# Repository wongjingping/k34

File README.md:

# k34

This project contains the pcb designs for the k34 keyboard. The k34 is a unibody, column-staggered, high-profile, 3d-printed, tray-mount keyboard with 34 keys.

`orient.py` contains a python script I used to programmatically arrange the switch and diode footprints. Traces were hand-connected.

`k34/plate and case reference` contains the exported svg's that I imported into fusion360 for modeling the case and plate files. 

`case` contains the stl files I used for the plate and case. The case supports the sides/outline of the pcb and fits well but isn't secured (ie would be fine if you're not planning to transport/move it around a lot). Note that the plate is non-symmetric and is adapted directly from the pcb's edge cut layer. 

## Firmware

- [zmk](https://github.com/wongjingping/zmk-config)

- [qmk](https://github.com/qmk/qmk_firmware/tree/master/keyboards/k34)

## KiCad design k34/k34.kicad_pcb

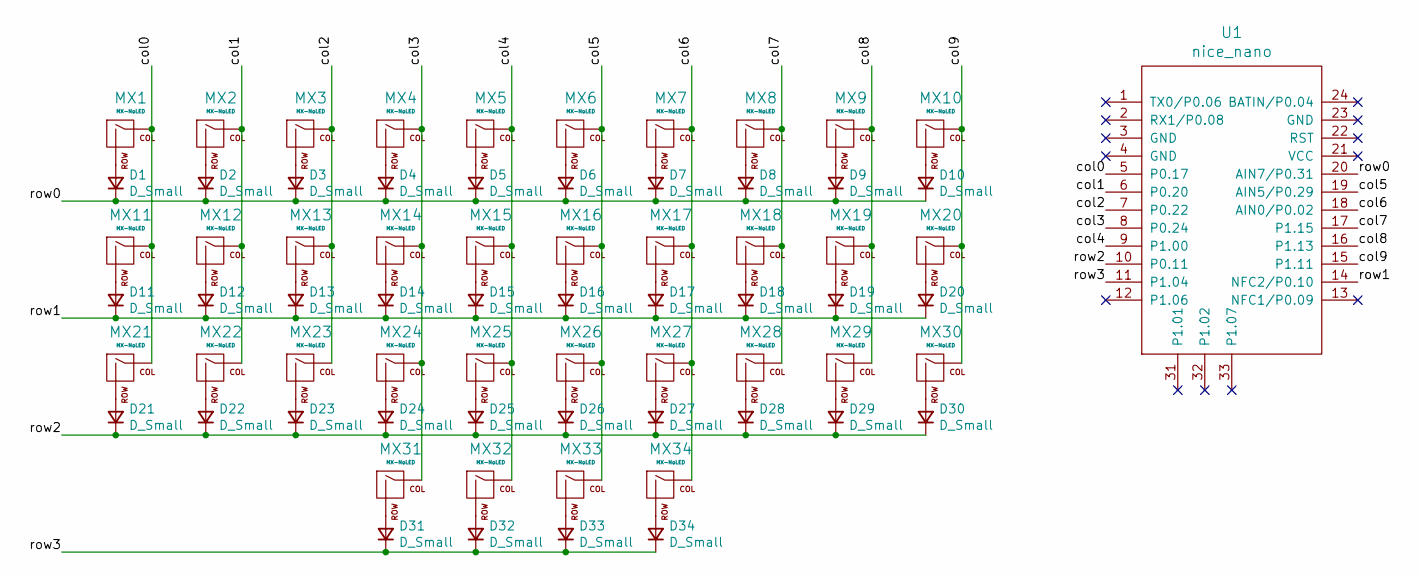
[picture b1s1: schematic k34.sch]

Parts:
D1, D2, D3, D4, D5, D6, D7, D8, D9, D10, D11, D12, D13, D14, D15, D16, D17, D18, D19, D20, D21, D22, D23, D24, D25, D26, D27, D28, D29, D30, D31, D32, D33, D34: D_Small; D_SOD-128
MX1, MX2, MX3, MX4, MX5, MX6, MX7, MX8, MX9, MX10, MX11, MX12, MX13, MX14, MX15, MX16, MX17, MX18, MX19, MX20, MX21, MX22, MX23, MX24, MX25, MX26, MX27, MX28, MX29, MX30, MX31, MX32, MX33, MX34: MX-NoLED; MXOnly-1U-Hotswap
U1: nice_nano

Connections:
/col0: MX1.1 (COL), MX11.1 (COL), MX21.1 (COL), U1.5 (P0.17)
/col1: MX2.1 (COL), MX12.1 (COL), MX22.1 (COL), U1.6 (P0.20)
/col2: MX3.1 (COL), MX13.1 (COL), MX23.1 (COL), U1.7 (P0.22)
/col3: MX4.1 (COL), MX14.1 (COL), MX24.1 (COL), MX31.1 (COL), U1.8 (P0.24)
/col4: MX5.1 (COL), MX15.1 (COL), MX25.1 (COL), MX32.1 (COL), U1.9 (P1.00)
/col5: MX6.1 (COL), MX16.1 (COL), MX26.1 (COL), MX33.1 (COL), U1.19 (AIN5/P0.29)
/col6: MX7.1 (COL), MX17.1 (COL), MX27.1 (COL), MX34.1 (COL), U1.18 (AIN0/P0.02)
/col7: MX8.1 (COL), MX18.1 (COL), MX28.1 (COL), U1.17 (P1.15)
/col8: MX9.1 (COL), MX19.1 (COL), MX29.1 (COL), U1.16 (P1.13)
/col9: MX10.1 (COL), MX20.1 (COL), MX30.1 (COL), U1.15 (P1.11)
/row0: D1.1 (K), D2.1 (K), D3.1 (K), D4.1 (K), D5.1 (K), D6.1 (K), D7.1 (K), D8.1 (K), D9.1 (K), D10.1 (K), U1.20 (AIN7/P0.31)
/row1: D11.1 (K), D12.1 (K), D13.1 (K), D14.1 (K), D15.1 (K), D16.1 (K), D17.1 (K), D18.1 (K), D19.1 (K), D20.1 (K), U1.14 (NFC2/P0.10)
/row2: D21.1 (K), D22.1 (K), D23.1 (K), D24.1 (K), D25.1 (K), D26.1 (K), D27.1 (K), D28.1 (K), D29.1 (K), D30.1 (K), U1.10 (P0.11)
/row3: D31.1 (K), D32.1 (K), D33.1 (K), D34.1 (K), U1.11 (P1.04)
unnamed: D1.2 (A), MX1.2 (ROW)
unnamed: D2.2 (A), MX2.2 (ROW)
unnamed: D3.2 (A), MX3.2 (ROW)
unnamed: D4.2 (A), MX4.2 (ROW)
unnamed: D5.2 (A), MX5.2 (ROW)
unnamed: D6.2 (A), MX6.2 (ROW)
unnamed: D7.2 (A), MX7.2 (ROW)
unnamed: D8.2 (A), MX8.2 (ROW)
unnamed: D9.2 (A), MX9.2 (ROW)
unnamed: D10.2 (A), MX10.2 (ROW)
unnamed: D11.2 (A), MX11.2 (ROW)
unnamed: D12.2 (A), MX12.2 (ROW)
unnamed: D13.2 (A), MX13.2 (ROW)
unnamed: D14.2 (A), MX14.2 (ROW)
unnamed: D15.2 (A), MX15.2 (ROW)
unnamed: D16.2 (A), MX16.2 (ROW)
unnamed: D17.2 (A), MX17.2 (ROW)
unnamed: D18.2 (A), MX18.2 (ROW)
unnamed: D19.2 (A), MX19.2 (ROW)
unnamed: D20.2 (A), MX20.2 (ROW)
unnamed: D21.2 (A), MX21.2 (ROW)
unnamed: D22.2 (A), MX22.2 (ROW)
unnamed: D23.2 (A), MX23.2 (ROW)
unnamed: D24.2 (A), MX24.2 (ROW)
unnamed: D25.2 (A), MX25.2 (ROW)
unnamed: D26.2 (A), MX26.2 (ROW)
unnamed: D27.2 (A), MX27.2 (ROW)
unnamed: D28.2 (A), MX28.2 (ROW)
unnamed: D29.2 (A), MX29.2 (ROW)
unnamed: D30.2 (A), MX30.2 (ROW)
unnamed: D31.2 (A), MX31.2 (ROW)
unnamed: D32.2 (A), MX32.2 (ROW)
unnamed: D33.2 (A), MX33.2 (ROW)
unnamed: D34.2 (A), MX34.2 (ROW)

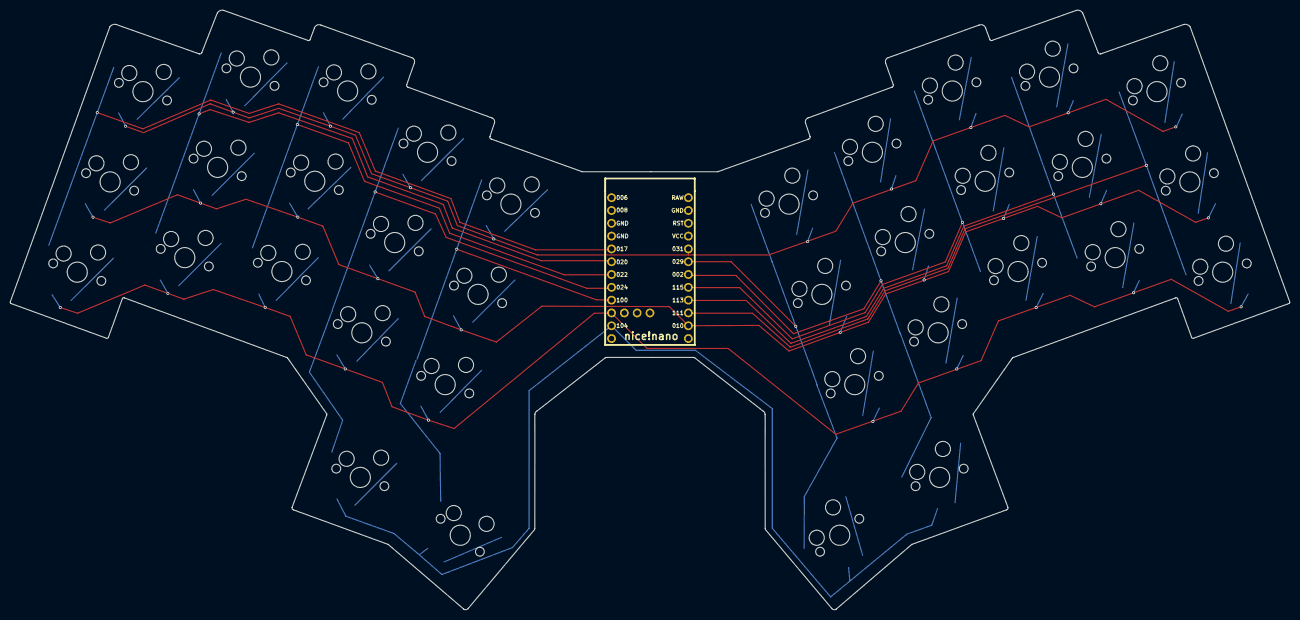
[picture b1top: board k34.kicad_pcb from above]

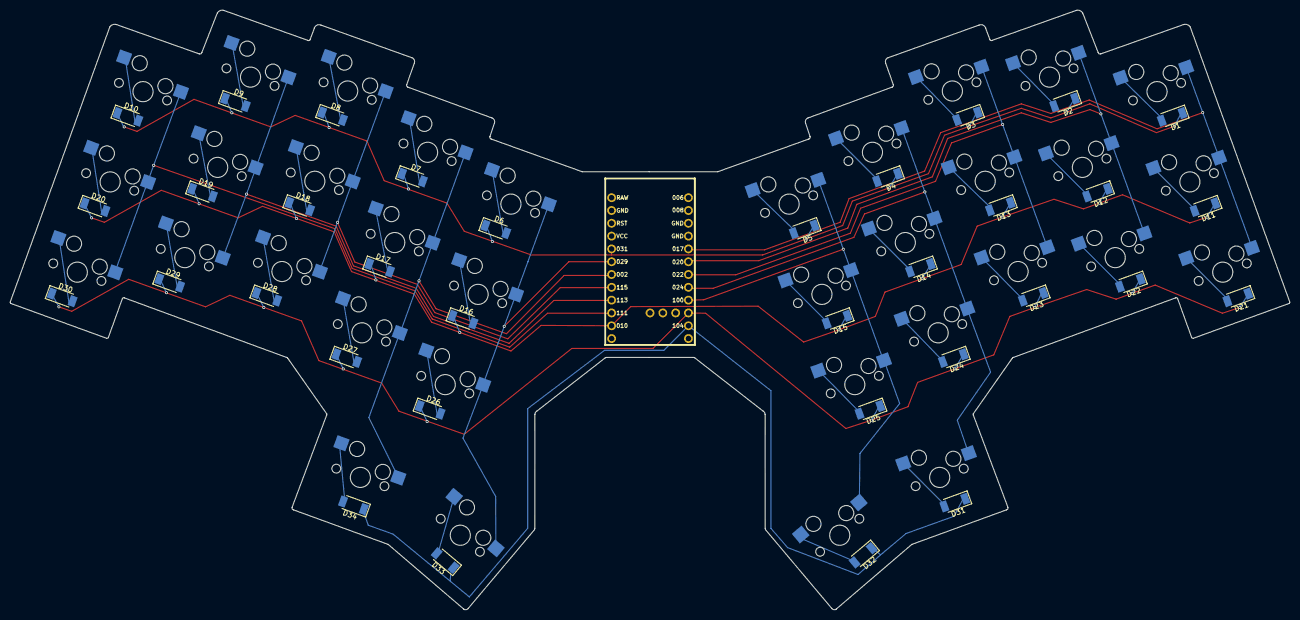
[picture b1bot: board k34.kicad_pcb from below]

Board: 2 copper layers, 253.8 x 118.9 mm, 69 parts (34 on the bottom side), 48 nets.

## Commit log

2021-09-26 init
2021-09-26 mark no connection
2021-09-29 added plate pcb
2021-10-03 added 3rd screw
2021-10-03 added case files
2021-11-06 updated pcb design and added case/plate stl files, img
2021-11-20 updated plates
2022-05-14 updated schematic with wider diode
2022-05-14 save kicad pro
2022-05-14 add case stl files
